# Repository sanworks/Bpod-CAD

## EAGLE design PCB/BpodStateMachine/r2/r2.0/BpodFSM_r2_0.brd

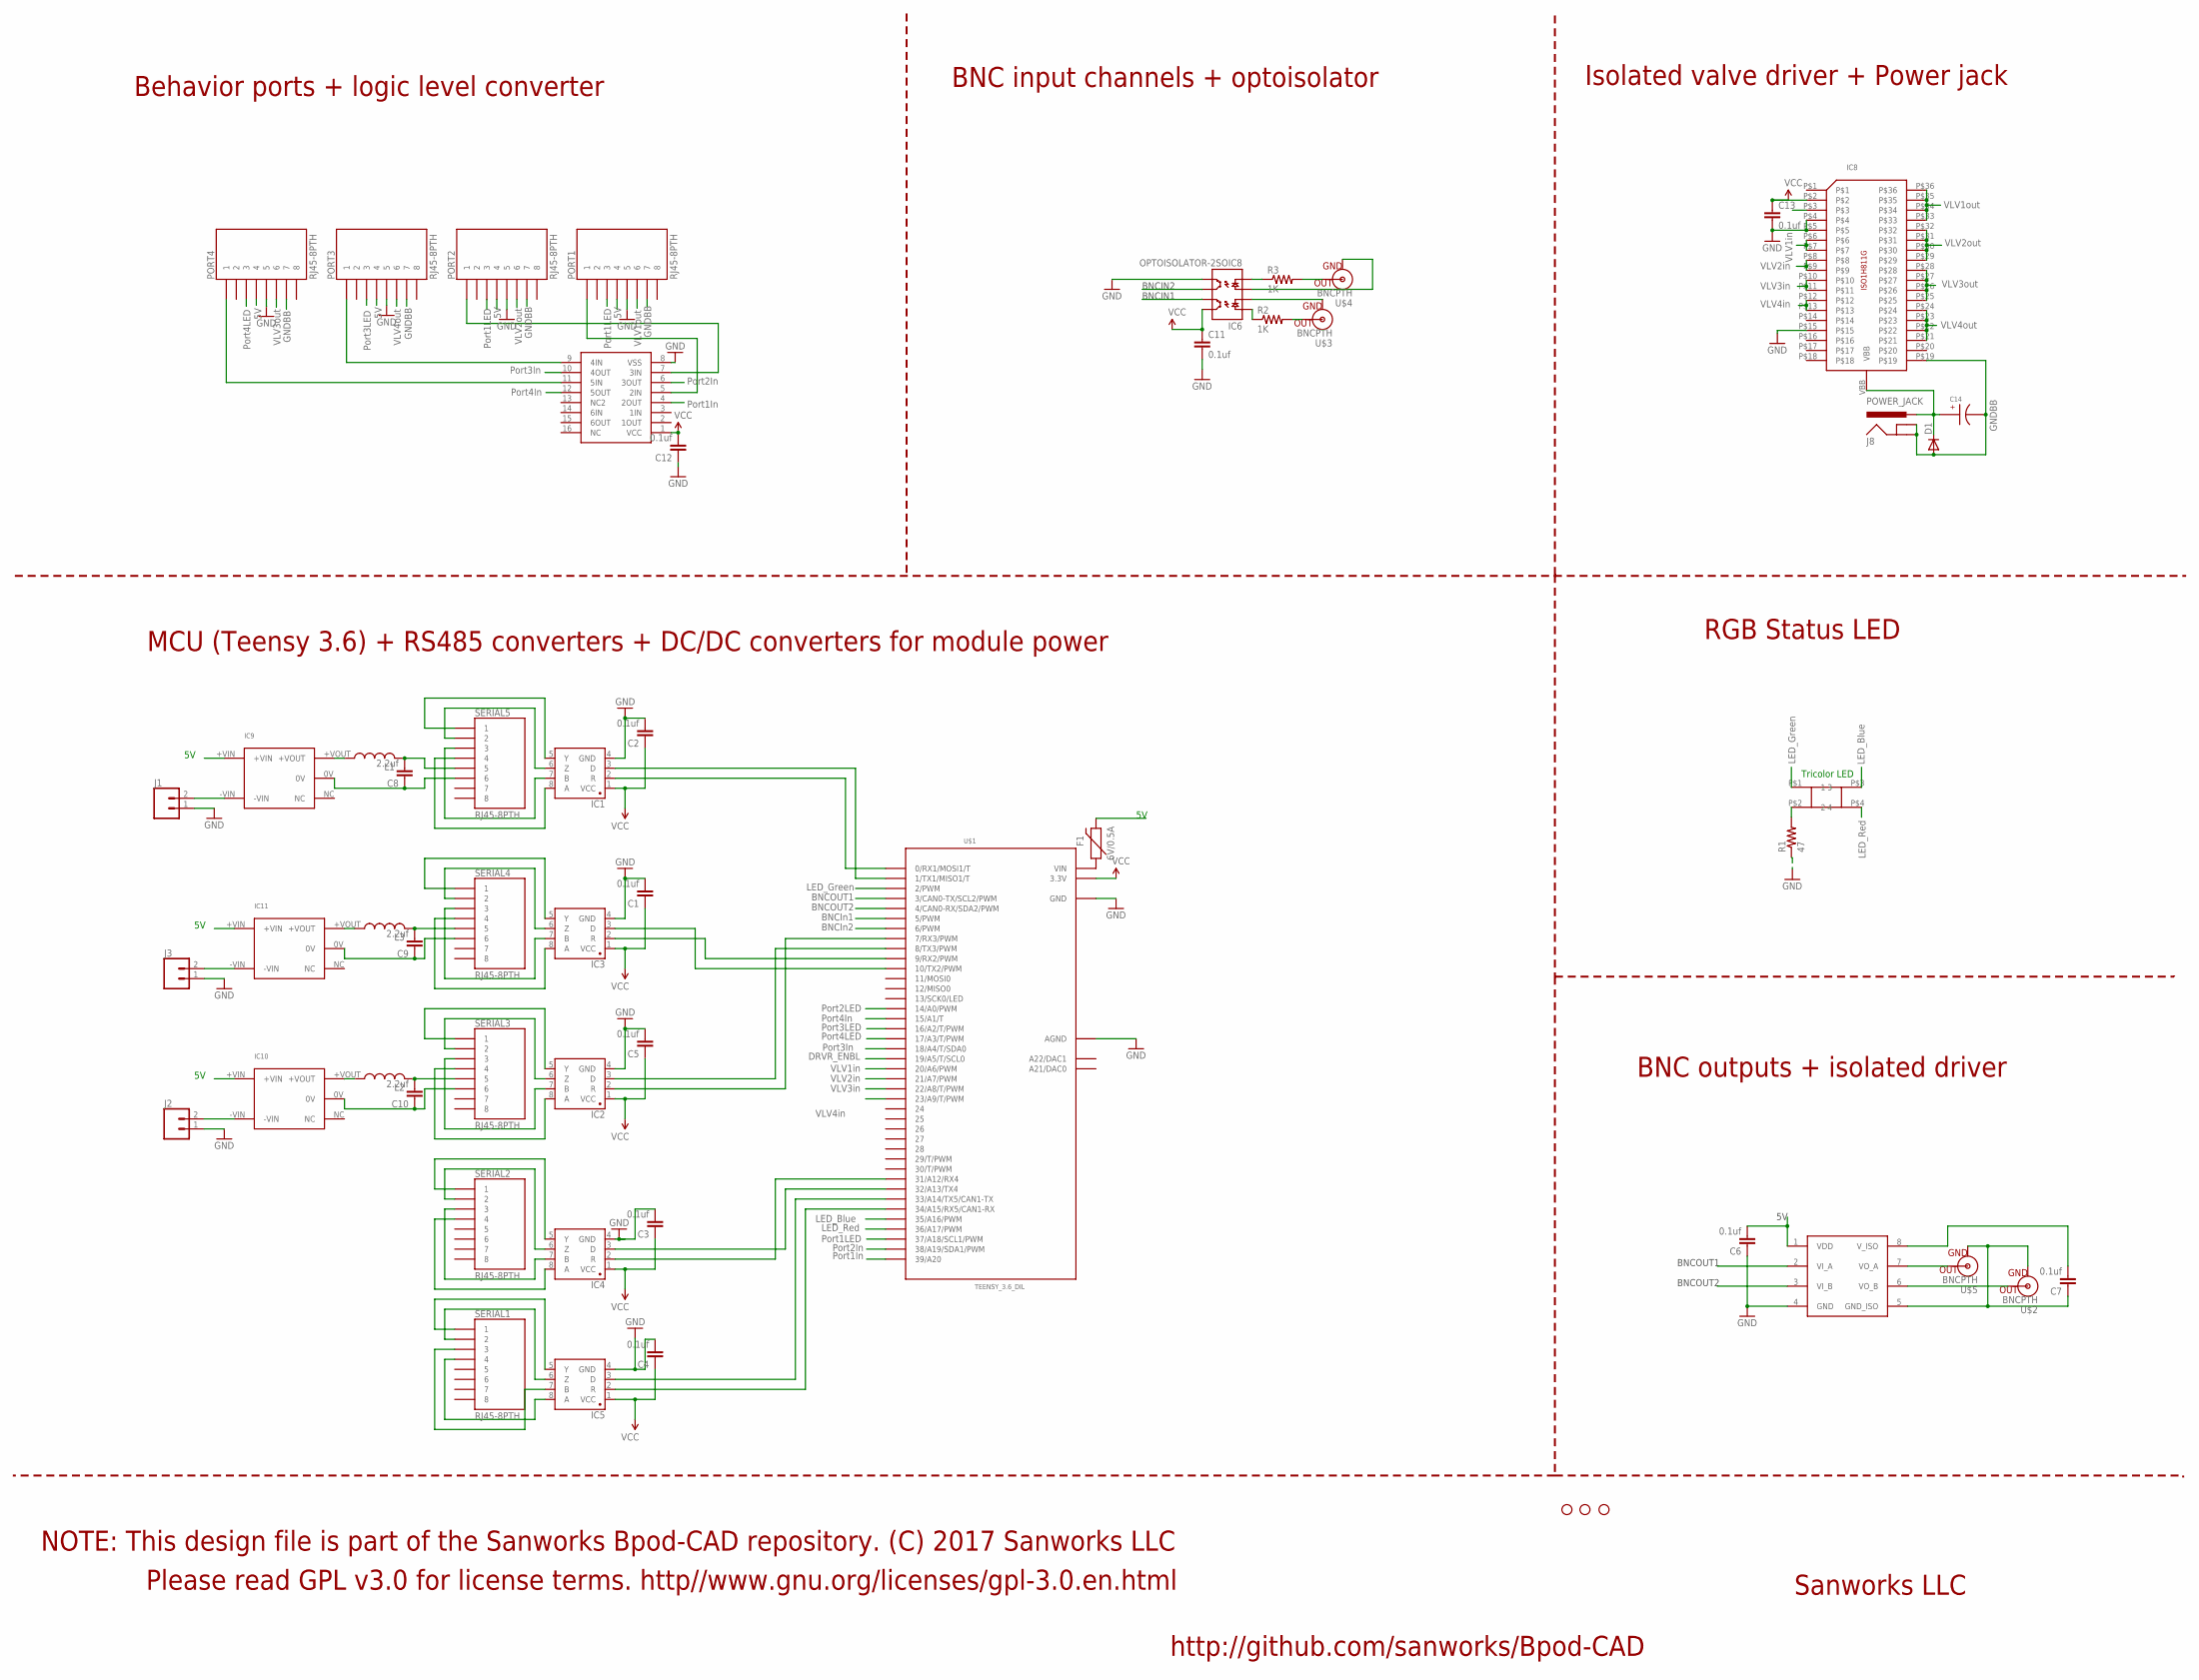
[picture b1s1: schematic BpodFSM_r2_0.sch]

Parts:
C1, C2, C3, C4, C5, C6, C7, C11, C12, C13: 0.1uf; 1206
C8, C9, C10: 2.2uf; 1206
C14: EEE-FK1H100UR
D1: DIODE-DO214AA; DO214AA
F1: 6V/0.5A; 1206
IC1, IC2, IC3, IC4, IC5: SN65HVD31DR; SO08
IC6: OPTOISOLATOR-2SOIC8; SO08-2
IC7: ADUM5240; SO08
IC8: ISO1H811G
IC9, IC10, IC11: MTU1D0505MC
IC12: CD4050; SO16
J1, J2, J3: CONN_02; 1X02
J8: POWER_JACK; POWER_JACK_PTH
JP3, JP4, JP5: STAND-OFF
L1, L2, L3: L-USL3225M; L3225M
PORT1, PORT2, PORT3, PORT4: RJ45-8PTH; RJ45-8
R1: 47; 1206
R2, R3: 1K; 1206
SERIAL1, SERIAL2, SERIAL3, SERIAL4, SERIAL5: RJ45-8PTH; RJ45-8
U$1: TEENSY_3.6_DIL
U$2, U$3, U$4, U$5: BNCPTH; BNC
U$8: SQUARE_TRICOLOR_LED

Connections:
5V: C6.2, F1.2, IC7.1 (VDD), IC9.+VIN, IC10.+VIN, IC11.+VIN, PORT1.4, PORT2.4, PORT3.4, PORT4.4
BNCIN1: IC6.7 (EM1), U$1.6 (6/PWM)
BNCIN2: IC6.6 (CL2), U$1.5 (5/PWM)
BNCOUT1: IC7.3 (VI_B), U$1.4 (4/CAN0-RX/SDA2/PWM)
BNCOUT2: IC7.2 (VI_A), U$1.3 (3/CAN0-TX/SCL2/PWM)
DRVR_ENBL: IC8.P$3, U$1.19/A5 (19/A5/T/SCL0)
GND: C1.2, C2.2, C3.2, C4.2, C5.2, C6.1, C11.2, C12.1, C13.2, IC1.4 (GND), IC2.4 (GND), IC3.4 (GND), IC4.4 (GND), IC5.4 (GND), IC6.5 (EM2), IC7.4 (GND), IC8.P$4, IC8.P$5, IC8.P$15, IC12.8 (VSS), J1.1, J2.1, J3.1, PORT1.5, PORT2.5, PORT3.5, PORT4.5, R1.1, U$1.AGND, U$1.GND, U$1.GND1 (GND)
GNDBB: C14.CATHODE, D1.A, IC8.P$19, J8.GND, J8.GNDBREAK, PORT1.7, PORT2.7, PORT3.7, PORT4.7
ISOGND: C7.1, IC7.5 (GND_ISO), U$2.GND, U$5.GND
LED_BLUE: U$1.35/A16 (35/A16/PWM), U$8.P$3 (3)
LED_GREEN: U$1.2 (2/PWM), U$8.P$1 (1)
LED_RED: U$1.36/A17 (36/A17/PWM), U$8.P$4 (4)
unnamed: IC3.8 (A), SERIAL4.4
unnamed: IC3.7 (B), SERIAL4.3
unnamed: IC3.6 (Z), SERIAL4.2
unnamed: IC3.5 (Y), SERIAL4.1
unnamed: IC3.2 (R), U$1.9 (9/RX2/PWM)
unnamed: IC3.3 (D), U$1.10 (10/TX2/PWM)
unnamed: IC1.8 (A), SERIAL5.4
unnamed: IC1.7 (B), SERIAL5.3
unnamed: IC1.6 (Z), SERIAL5.2
unnamed: IC1.5 (Y), SERIAL5.1
unnamed: IC1.2 (R), U$1.0 (0/RX1/MOSI1/T)
unnamed: IC1.3 (D), U$1.1 (1/TX1/MISO1/T)
unnamed: IC6.3 (A2), U$4.GND
unnamed: R3.2, U$4.S (OUT)
unnamed: R2.2, U$3.S (OUT)
unnamed: IC6.2 (C1), U$3.GND
unnamed: IC2.8 (A), SERIAL3.4
unnamed: IC2.7 (B), SERIAL3.3
unnamed: IC2.6 (Z), SERIAL3.2
unnamed: IC12.7 (3IN), PORT2.1
unnamed: IC2.5 (Y), SERIAL3.1
unnamed: IC2.2 (R), U$1.7 (7/RX3/PWM)
unnamed: C8.2, L1.2, SERIAL5.5
unnamed: IC12.9 (4IN), PORT3.1
unnamed: R1.2, U$8.P$2 (2)
unnamed: C8.1, IC9.0V, SERIAL5.6
unnamed: IC7.7 (VO_A), U$5.S (OUT)
unnamed: IC2.3 (D), U$1.8 (8/TX3/PWM)
unnamed: F1.1, U$1.VIN
unnamed: IC7.6 (VO_B), U$2.S (OUT)
unnamed: IC12.11 (5IN), PORT4.1
unnamed: IC5.8 (A), SERIAL1.4
unnamed: IC5.7 (B), SERIAL1.3
unnamed: IC5.6 (Z), SERIAL1.2
unnamed: IC5.5 (Y), SERIAL1.1
unnamed: IC4.8 (A), SERIAL2.4
unnamed: IC4.7 (B), SERIAL2.3
unnamed: IC4.6 (Z), SERIAL2.2
unnamed: IC9.+VOUT, L1.1
unnamed: IC4.5 (Y), SERIAL2.1
unnamed: IC9.-VIN, J1.2
unnamed: IC5.2 (R), U$1.34/A15 (34/A15/RX5/CAN1-RX)
unnamed: C10.1, IC10.0V, SERIAL3.6
unnamed: C10.2, L2.2, SERIAL3.5
unnamed: IC10.+VOUT, L2.1
unnamed: IC10.-VIN, J2.2
unnamed: C9.1, IC11.0V, SERIAL4.6
unnamed: IC5.3 (D), U$1.33/A14 (33/A14/TX5/CAN1-TX)
unnamed: C9.2, L3.2, SERIAL4.5
unnamed: IC11.+VOUT, L3.1
unnamed: IC11.-VIN, J3.2
unnamed: IC4.2 (R), U$1.31/A12 (31/A12/RX4)
unnamed: IC4.3 (D), U$1.32/A13 (32/A13/TX4)
unnamed: IC6.1 (A1), R2.1
unnamed: IC6.4 (C2), R3.1
unnamed: IC12.5 (2IN), PORT1.1
unnamed: C7.2, IC7.8 (V_ISO)
PORT1IN: IC12.4 (2OUT), U$1.39/A20
PORT1LED: PORT1.3, U$1.37/A18 (37/A18/SCL1/PWM)
PORT2IN: IC12.6 (3OUT), U$1.38/A19 (38/A19/SDA1/PWM)
PORT2LED: PORT2.3, U$1.14/A0 (14/A0/PWM)
PORT3IN: IC12.10 (4OUT), U$1.18/A4 (18/A4/T/SDA0)
PORT3LED: PORT3.3, U$1.16/A2 (16/A2/T/PWM)
PORT4IN: IC12.12 (5OUT), U$1.15/A1 (15/A1/T)
PORT4LED: PORT4.3, U$1.17/A3 (17/A3/T/PWM)
VBB: C14.ANODE, D1.C, IC8.VBB, J8.PWR
VCC: C1.1, C2.1, C3.1, C4.1, C5.1, C11.1, C12.2, C13.1, IC1.1 (VCC), IC2.1 (VCC), IC3.1 (VCC), IC4.1 (VCC), IC5.1 (VCC), IC6.8 (CL1), IC8.P$2, IC12.1 (VCC), U$1.3.3V, U$1.3.3V3 (3.3V)
VLV1IN: IC8.P$6, IC8.P$7, U$1.23/A9 (23/A9/T/PWM)
VLV1OUT: IC8.P$33, IC8.P$34, IC8.P$35, IC8.P$36, PORT1.6
VLV2IN: IC8.P$8, IC8.P$9, U$1.22/A8 (22/A8/T/PWM)
VLV2OUT: IC8.P$29, IC8.P$30, IC8.P$31, IC8.P$32, PORT2.6
VLV3IN: IC8.P$12, IC8.P$13, U$1.20/A6 (20/A6/PWM)
VLV3OUT: IC8.P$21, IC8.P$22, IC8.P$23, IC8.P$24, PORT3.6
VLV4IN: IC8.P$10, IC8.P$11, U$1.21/A7 (21/A7/PWM)
VLV4OUT: IC8.P$25, IC8.P$26, IC8.P$27, IC8.P$28, PORT4.6

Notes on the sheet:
Tricolor LED
LED_Blue
LED_Red
LED_Green
BNCIN1
BNCIN2
BNCIn1
BNCIn2
BNCOUT2
BNCOUT1
Port1In
Port2In
Port3In
Port4In
Port1LED
Port2LED
Port3LED
Port4LED
DRVR_ENBL
VLV2in
VLV3in
VLV4in
VLV1in
GNDBB
VLV1out
VLV2out
VLV3out
VLV4out
Sanworks LLC
http://github.com/sanworks/Bpod-CAD
Please read GPL v3.0 for license terms. http//www.gnu.org/licenses/gpl-3.0.en.html
NOTE: This design file is part of the Sanworks Bpod-CAD repository. (C) 2017 Sanworks LLC
Behavior ports + logic level converter
BNC input channels + optoisolator
Isolated valve driver + Power jack
RGB Status LED
BNC outputs + isolated driver
MCU (Teensy 3.6) + RS485 converters + DC/DC converters for module power

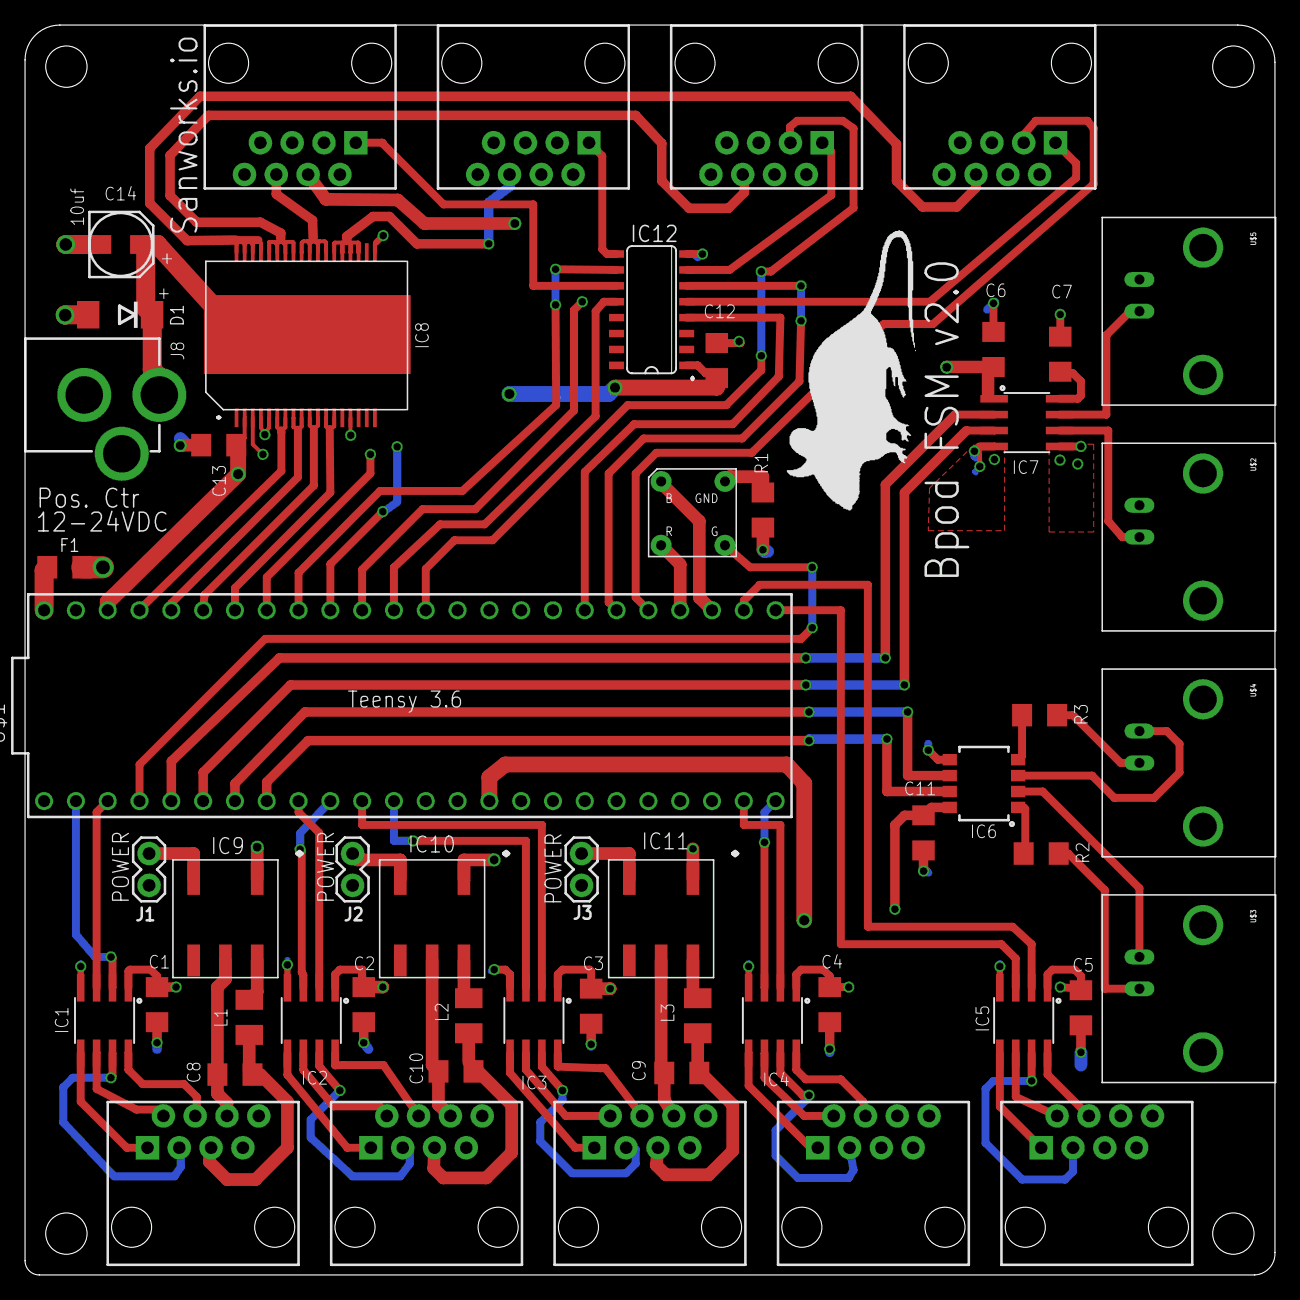
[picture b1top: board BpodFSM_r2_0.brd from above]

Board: 4 copper layers, 99.8 x 99.8 mm, 58 parts (0 on the bottom side), 87 nets.

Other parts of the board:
JP1: STAND-OFF
U$9: MOUSELOGO

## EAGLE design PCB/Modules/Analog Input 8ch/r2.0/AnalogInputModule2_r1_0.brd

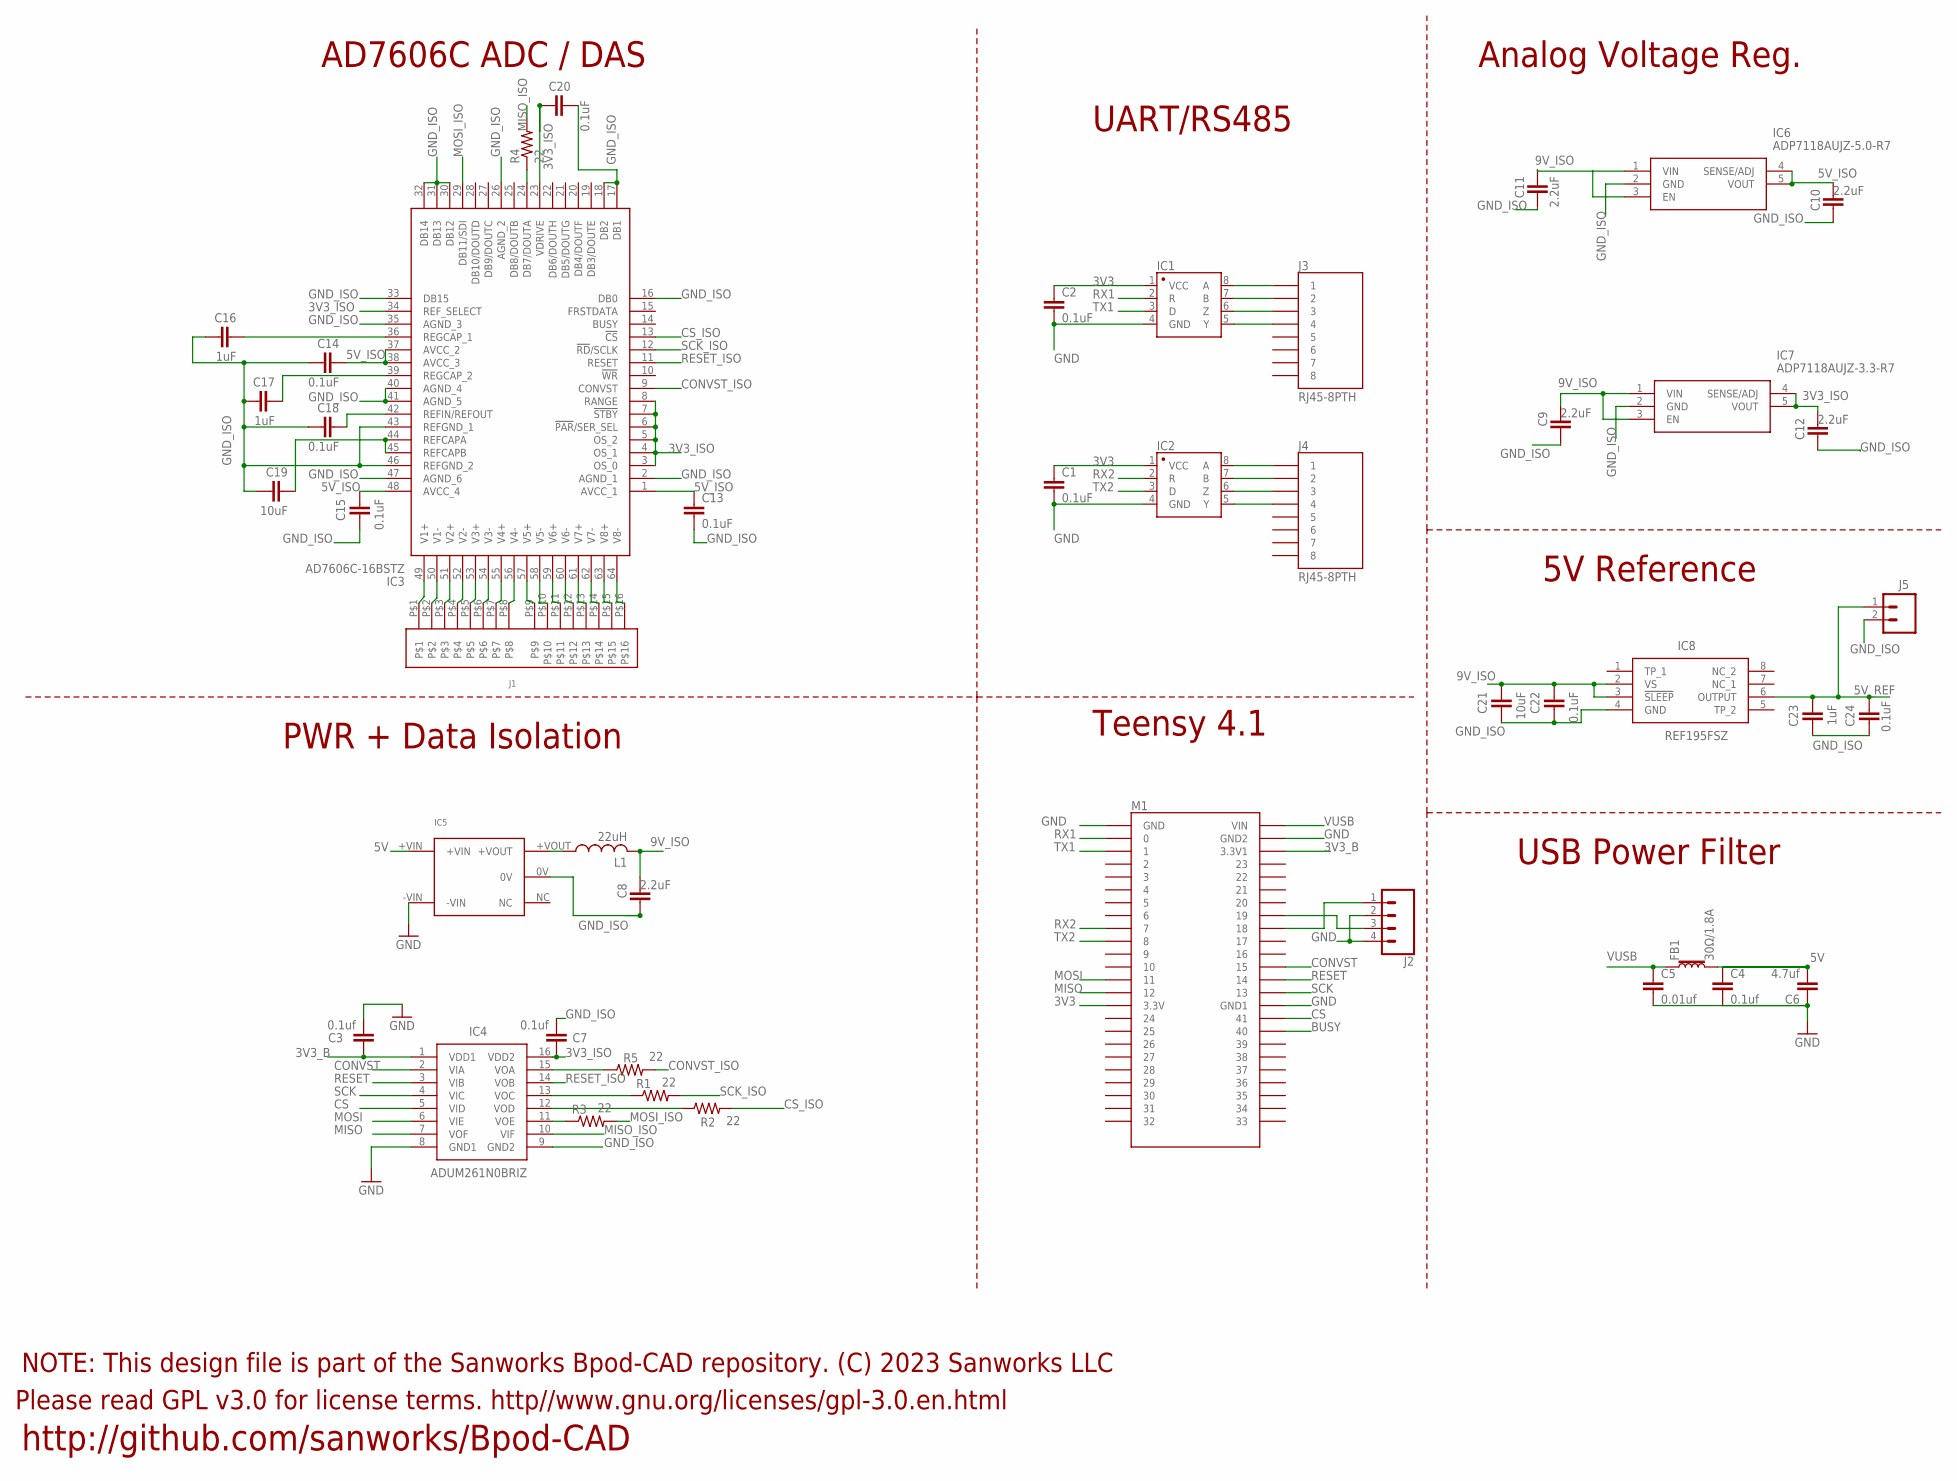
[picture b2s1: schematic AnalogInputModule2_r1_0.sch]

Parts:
C1, C2, C13, C14, C15, C18, C20, C22, C24: 0.1uF; 0805
C3, C4, C7: 0.1uf; 0805
C5: 0.01uf; 0805
C6: 4.7uf; 1206@2
C8, C9, C10, C11, C12: 2.2uF; 0805
C16, C17, C23: 1uF; 0805
C19, C21: 10uF; 0805
FB1: 30Ω/1.8A; 0603
IC1, IC2: SN65HVD31DR; SO08
IC3: AD7606C-16BSTZ; QFP50P1200X1200X160-64N
IC4: ADUM261N0BRIZ; SOIC127P1030X264-16N
IC5: 5V; MTU1D0505MC
IC6: ADP7118AUJZ-5.0-R7; SOT95P280X100-5N
IC7: ADP7118AUJZ-3.3-R7; SOT95P280X100-5N
IC8: REF195FSZ; SOIC127P600X175-8N
J1: 16POS_MOLEX_SOCKET
J2: CONN_04SCREW_LOCK; SCREWTERMINAL-3.5MM-4_LOCK
J3, J4: RJ45-8PTH; RJ45-8
J5: CONN_023.5MM_LOCK; SCREWTERMINAL-3.5MM-2_LOCK
L1: 22uH; L3225M
M1: TEENSY4.1_SIDESONLY
R1, R2, R3, R4, R5: 22; R0805

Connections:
3V3: C1.1, C2.1, IC1.1 (VCC), IC2.1 (VCC), M1.3V3 (3.3V)
3V3_B: C3.1, IC4.1 (VDD1), M1.3V3_LO (3.3V1)
3V3_ISO: C7.1, C12.2, C20.1, IC3.3 (OS_0), IC3.4 (OS_1), IC3.5 (OS_2), IC3.6 (!PAR!/SER_SEL), IC3.7 (!STBY), IC3.8 (RANGE), IC3.23 (VDRIVE), IC3.34 (REF_SELECT), IC4.16 (VDD2), IC7.4 (SENSE/ADJ), IC7.5 (VOUT)
5V: C4.1, C6.2, FB1.2, IC5.+VIN
5V_ISO: C10.2, C13.1, C14.2, C15.2, IC3.1 (AVCC_1), IC3.37 (AVCC_2), IC3.38 (AVCC_3), IC3.48 (AVCC_4), IC6.4 (SENSE/ADJ), IC6.5 (VOUT)
5V_REF: C23.2, C24.2, IC8.6 (OUTPUT), J5.1
9V_ISO: C8.2, C9.2, C11.2, C21.2, C22.2, IC6.1 (VIN), IC6.3 (EN), IC7.1 (VIN), IC7.3 (EN), IC8.2 (VS), IC8.3 (!SLEEP), L1.2
BUSY: M1.40
CONVST: IC4.2 (VIA), M1.15/A1 (15)
CONVST_ISO: IC3.9 (CONVST), R5.2
CS: IC4.5 (VID), M1.41
CS_ISO: IC3.13 (!CS), R2.2
GND: C1.2, C2.2, C3.2, C4.2, C5.2, C6.1, IC1.4 (GND), IC2.4 (GND), IC4.8 (GND1), IC5.-VIN, J2.2, J2.4, M1.AGND (GND), M1.GND (GND1), M1.GND1 (GND2)
GND_ISO: C7.2, C8.1, C9.1, C10.1, C11.1, C12.1, C13.2, C14.1, C15.1, C16.1, C17.1, C18.1, C19.1, C20.2, C21.1, C22.1, C23.1, C24.1, IC3.2 (AGND_1), IC3.16 (DB0), IC3.17 (DB1), IC3.18 (DB2), IC3.26 (AGND_2), IC3.30 (DB12), IC3.31 (DB13), IC3.32 (DB14), IC3.33 (DB15), IC3.35 (AGND_3), IC3.40 (AGND_4), IC3.41 (AGND_5), IC3.43 (REFGND_1), IC3.46 (REFGND_2), IC3.47 (AGND_6), IC4.9 (GND2), IC5.0V, IC6.2 (GND), IC7.2 (GND), IC8.4 (GND), J5.2
MISO: IC4.7 (VOF), M1.12/MISO (12)
MISO_ISO: IC4.10 (VIF), R4.2
MOSI: IC4.6 (VIE), M1.11/MOSI (11)
MOSI_ISO: IC3.29 (DB11/SDI), R3.2
unnamed: IC1.6 (Z), J3.3
unnamed: IC1.8 (A), J3.1
unnamed: IC1.5 (Y), J3.4
unnamed: IC1.7 (B), J3.2
unnamed: IC2.6 (Z), J4.3
unnamed: IC2.5 (Y), J4.4
unnamed: IC2.8 (A), J4.1
unnamed: IC2.7 (B), J4.2
unnamed: IC3.64 (V8-), J1.P$16
unnamed: IC3.63 (V8+), J1.P$15
unnamed: IC3.62 (V7-), J1.P$14
unnamed: IC3.61 (V7+), J1.P$13
unnamed: IC3.60 (V6-), J1.P$12
unnamed: IC3.59 (V6+), J1.P$11
unnamed: IC3.58 (V5-), J1.P$10
unnamed: IC3.57 (V5+), J1.P$9
unnamed: IC3.56 (V4-), J1.P$8
unnamed: IC3.55 (V4+), J1.P$7
unnamed: IC3.54 (V3-), J1.P$6
unnamed: IC3.53 (V3+), J1.P$5
unnamed: IC3.52 (V2-), J1.P$4
unnamed: IC3.51 (V2+), J1.P$3
unnamed: IC3.50 (V1-), J1.P$2
unnamed: IC3.49 (V1+), J1.P$1
unnamed: IC4.13 (VOC), R1.1
unnamed: IC4.12 (VOD), R2.1
unnamed: IC4.11 (VOE), R3.1
unnamed: IC3.24 (DB7/DOUTA), R4.1
unnamed: IC4.15 (VOA), R5.1
unnamed: C16.2, IC3.36 (REGCAP_1)
unnamed: C17.2, IC3.39 (REGCAP_2)
unnamed: C18.2, IC3.42 (REFIN/REFOUT)
unnamed: C19.2, IC3.44 (REFCAPA), IC3.45 (REFCAPB)
unnamed: J2.1, M1.18/A4/SDA (18)
unnamed: IC5.+VOUT, L1.1
unnamed: J2.3, M1.19/A5/SCL (19)
RESET: IC4.3 (VIB), M1.14/A0 (14)
RESET_ISO: IC3.11 (RESET), IC4.14 (VOB)
RX1: IC1.2 (R), M1.0/RX (0)
RX2: IC2.2 (R), M1.7
SCK: IC4.4 (VIC), M1.13/SCK (13)
SCK_ISO: IC3.12 (!RD!/SCLK), R1.2
TX1: IC1.3 (D), M1.1/TX (1)
TX2: IC2.3 (D), M1.8
VUSB: C5.1, FB1.1, M1.VIN

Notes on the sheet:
Teensy 4.1
UART/RS485
USB Power Filter
AD7606C ADC / DAS
PWR + Data Isolation
Analog Voltage Reg.
5V Reference
Please read GPL v3.0 for license terms. http//www.gnu.org/licenses/gpl-3.0.en.html
NOTE: This design file is part of the Sanworks Bpod-CAD repository. (C) 2023 Sanworks LLC
http://github.com/sanworks/Bpod-CAD

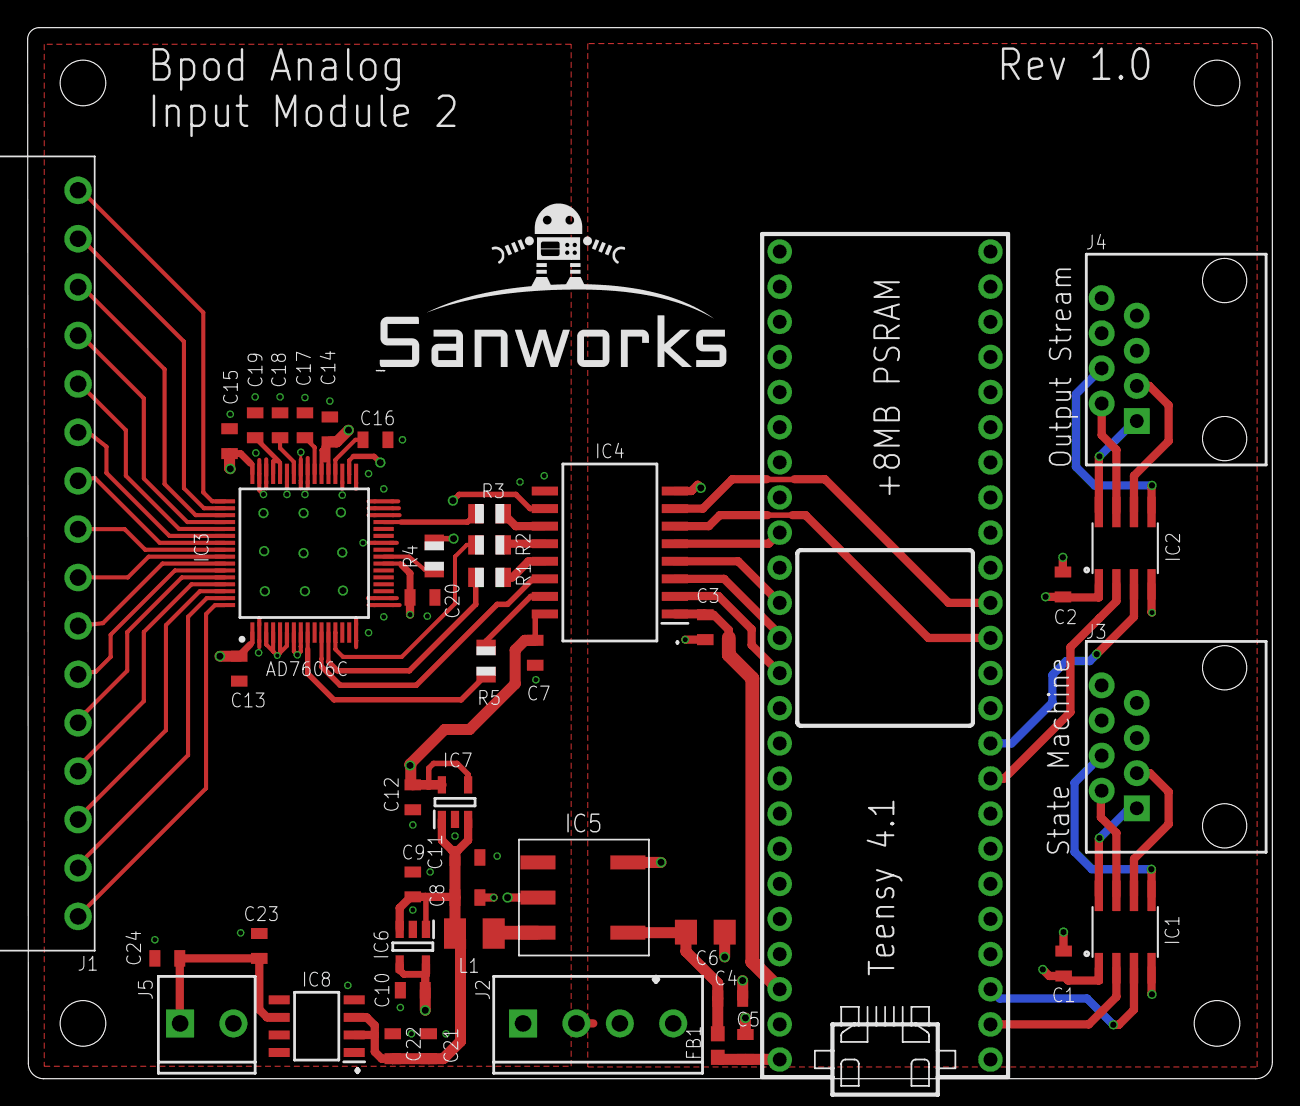
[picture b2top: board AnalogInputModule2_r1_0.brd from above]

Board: 4 copper layers, 90.0 x 76.0 mm, 50 parts (0 on the bottom side), 62 nets.

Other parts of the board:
U$1: SANWORKS_LOGO
U$5, U$6, U$7, U$8: STAND-OFF

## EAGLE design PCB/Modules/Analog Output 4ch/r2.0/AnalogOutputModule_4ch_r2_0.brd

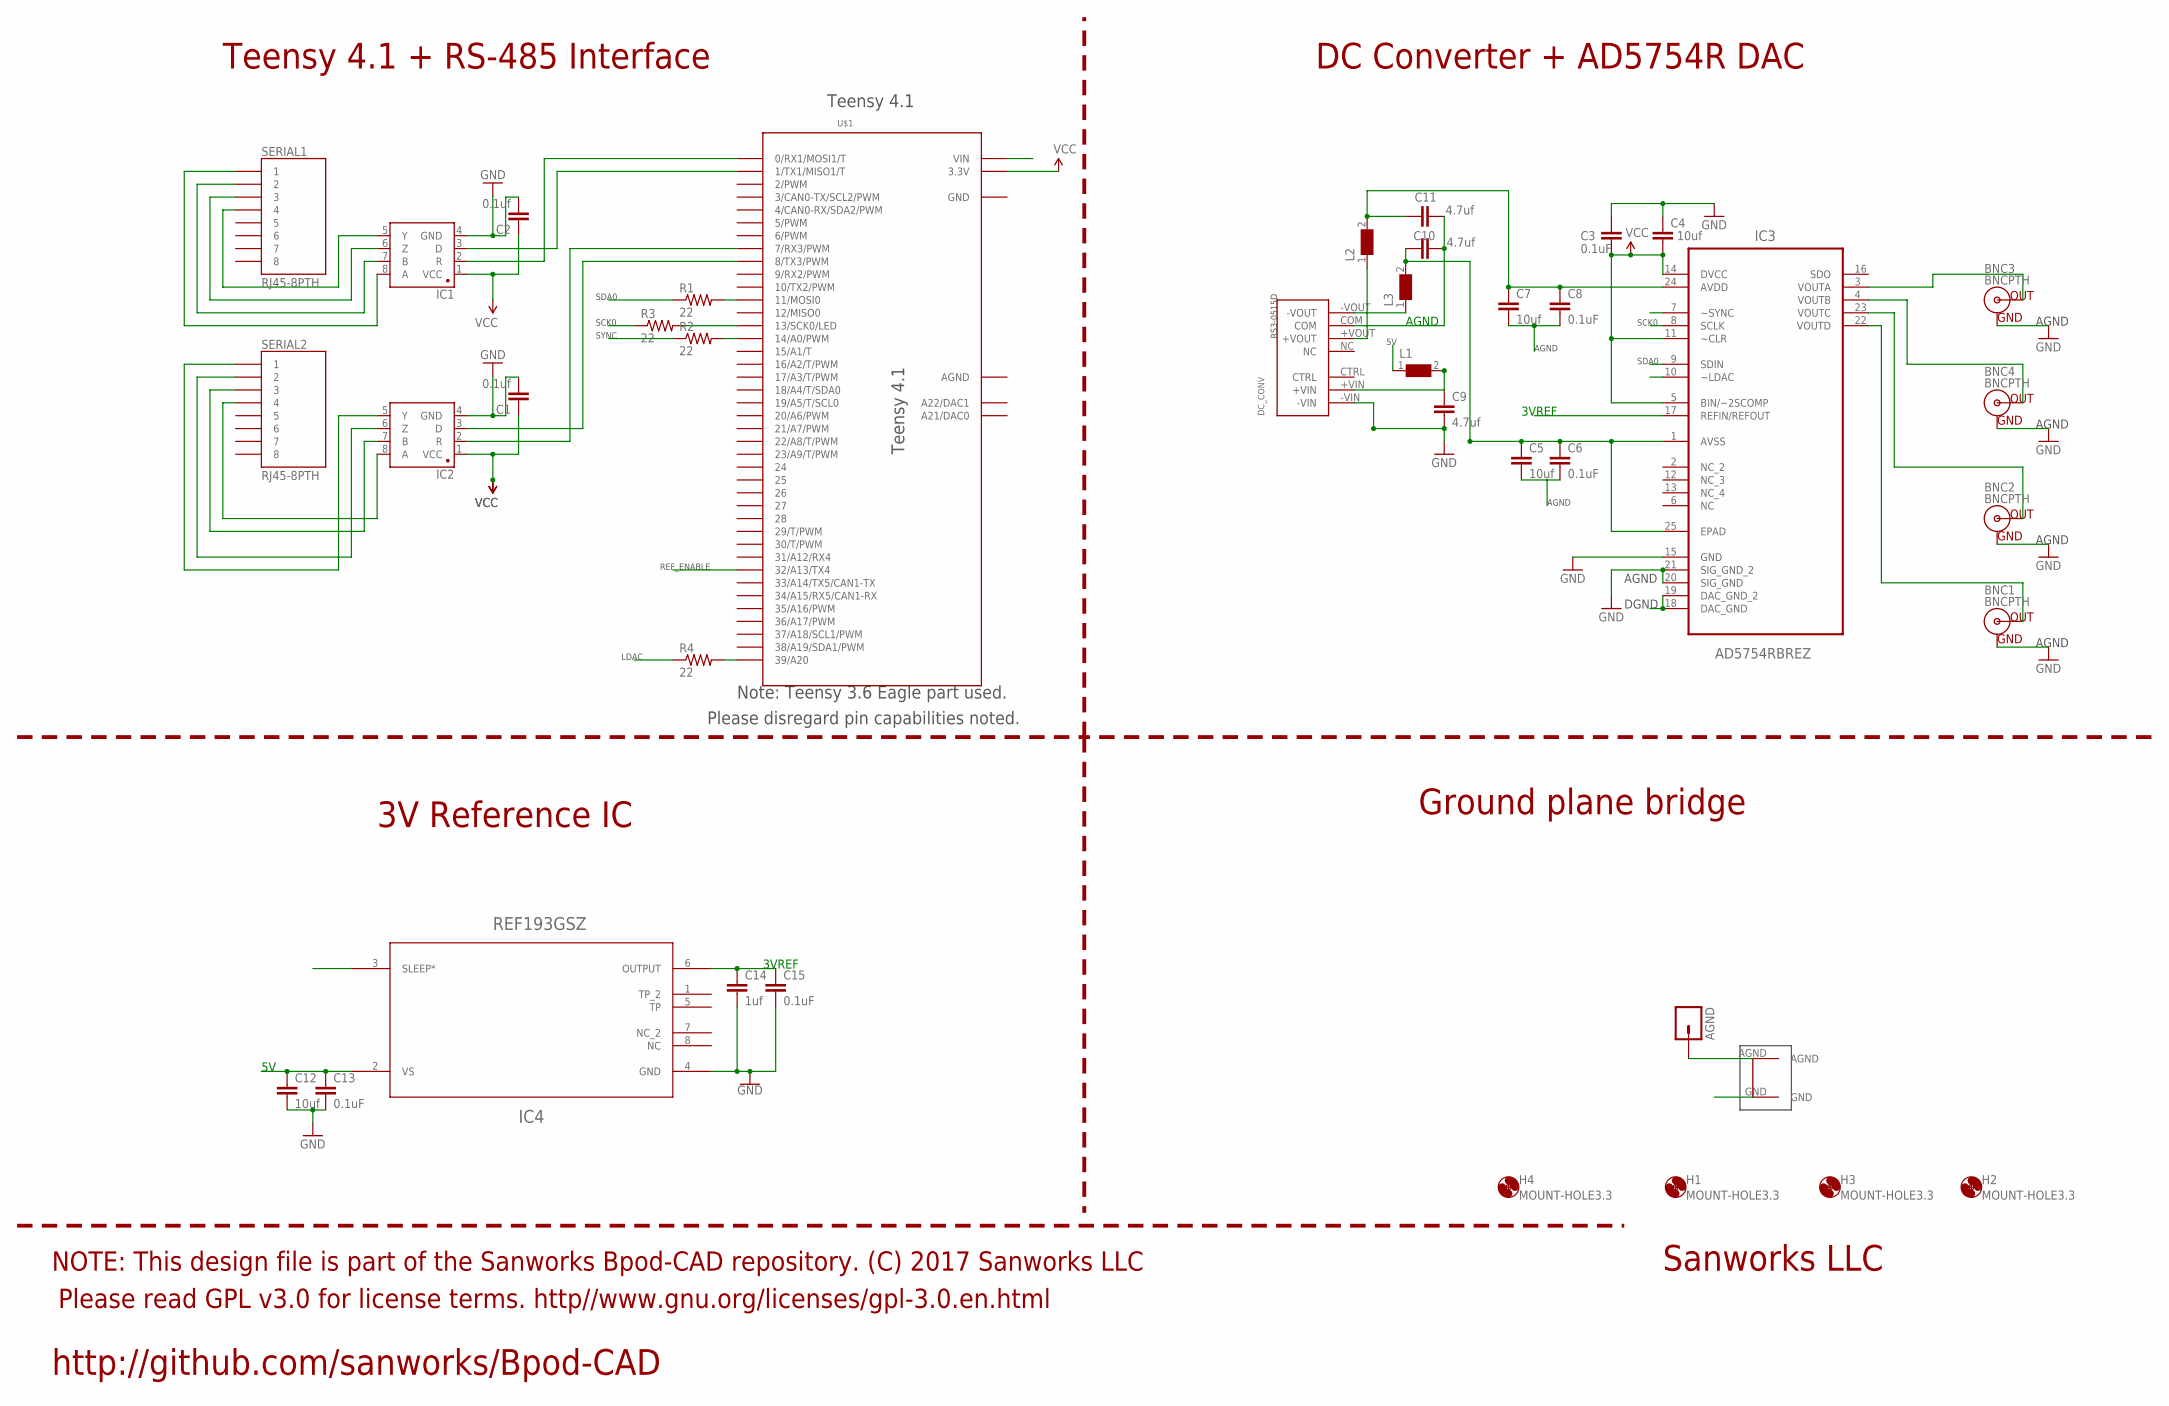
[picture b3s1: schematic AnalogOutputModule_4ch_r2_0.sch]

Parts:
AGND: M01PTH; 1X01
BNC1, BNC2, BNC3, BNC4: BNCPTH; BNC
C1, C2: 0.1uf; 1206@1
C3, C6, C8, C13, C15: 0.1uF; 0805
C4, C5, C7, C12: 10uf; 1206@1
C9, C10, C11: 4.7uf; 1206@1
C14: 1uf; 1206@1
DC_CONV: RS3-0515D
H1, H2, H3, H4: MOUNT-HOLE3.3; 3,3
IC1, IC2: SN65HVD31DR; SO08
IC3: AD5754RBREZ; SOP65P640X120-25N
IC4: REF193GSZ; R_8
L1, L2, L3: WE-CBF-742792118_1206; 1206
R1, R2, R3, R4: 22; 1206
SERIAL1, SERIAL2: RJ45-8PTH; RJ45-8
U$1: TEENSY_3.6_DIL
U$6: GNDPLANESHRT

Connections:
3VREF: C14.1, C15.1, IC3.17 (REFIN/REFOUT), IC4.6 (OUTPUT)
5V: C3.2, C4.2, C12.1, C13.1, IC3.5 (BIN/~2SCOMP), IC3.11 (~CLR), IC3.14 (DVCC), IC4.2 (VS), L1.1, U$1.VIN
AGND: AGND.1, BNC1.GND, BNC2.GND, BNC3.GND, BNC4.GND, C5.2, C6.2, C7.2, C8.2, C10.1, C11.2, DC_CONV.COM, IC3.18 (DAC_GND), IC3.19 (DAC_GND_2), IC3.20 (SIG_GND), IC3.21 (SIG_GND_2), U$1.AGND, U$6.AGND
GND: C1.2, C2.2, C3.1, C4.1, C9.2, C12.2, C13.2, C14.2, C15.2, DC_CONV.-VIN, IC1.4 (GND), IC2.4 (GND), IC3.15 (GND), IC4.4 (GND), U$1.GND, U$1.GND1 (GND), U$6.GND
LDAC: IC3.10 (~LDAC), R4.1
unnamed: IC1.3 (D), U$1.1 (1/TX1/MISO1/T)
unnamed: IC1.2 (R), U$1.0 (0/RX1/MOSI1/T)
unnamed: IC2.8 (A), SERIAL2.4
unnamed: IC2.7 (B), SERIAL2.3
unnamed: IC2.6 (Z), SERIAL2.2
unnamed: IC2.5 (Y), SERIAL2.1
unnamed: IC2.3 (D), U$1.8 (8/TX3/PWM)
unnamed: IC2.2 (R), U$1.7 (7/RX3/PWM)
unnamed: BNC3.S (OUT), IC3.3 (VOUTA)
unnamed: BNC4.S (OUT), IC3.4 (VOUTB)
unnamed: BNC2.S (OUT), IC3.23 (VOUTC)
unnamed: BNC1.S (OUT), IC3.22 (VOUTD)
unnamed: R1.2, U$1.11 (11/MOSI0)
unnamed: R3.2, U$1.13 (13/SCK0/LED)
unnamed: DC_CONV.-VOUT, L3.1
unnamed: DC_CONV.+VOUT, L2.1
unnamed: R2.2, U$1.14/A0 (14/A0/PWM)
unnamed: R4.2, U$1.39/A20
unnamed: IC1.8 (A), SERIAL1.1
unnamed: IC1.7 (B), SERIAL1.2
unnamed: IC1.6 (Z), SERIAL1.3
unnamed: IC1.5 (Y), SERIAL1.4
unnamed: C7.1, C8.1, C10.2, IC3.24 (AVDD), L2.2
unnamed: C9.1, DC_CONV.+VIN, L1.2
REF_ENABLE: IC4.3 (SLEEP*), U$1.32/A13 (32/A13/TX4)
SCK0: IC3.8 (SCLK), R3.1
SDA0: IC3.9 (SDIN), R1.1
SYNC: IC3.7 (~SYNC), R2.1
VCC: C1.1, C2.1, IC1.1 (VCC), IC2.1 (VCC), U$1.3.3V, U$1.3.3V3 (3.3V)
VSS: C5.1, C6.1, C11.1, IC3.1 (AVSS), IC3.25 (EPAD), L3.2

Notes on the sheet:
AGND
SCK0
SDA0
DGND
SYNC
LDAC
3VREF
REF_ENABLE
Teensy 4.1 + RS-485 Interface
DC Converter + AD5754R DAC
3V Reference IC
Ground plane bridge
Please read GPL v3.0 for license terms. http//www.gnu.org/licenses/gpl-3.0.en.html
NOTE: This design file is part of the Sanworks Bpod-CAD repository. (C) 2017 Sanworks LLC
Sanworks LLC
http://github.com/sanworks/Bpod-CAD
Teensy 4.1
Note: Teensy 3.6 Eagle part used.
Please disregard pin capabilities noted.

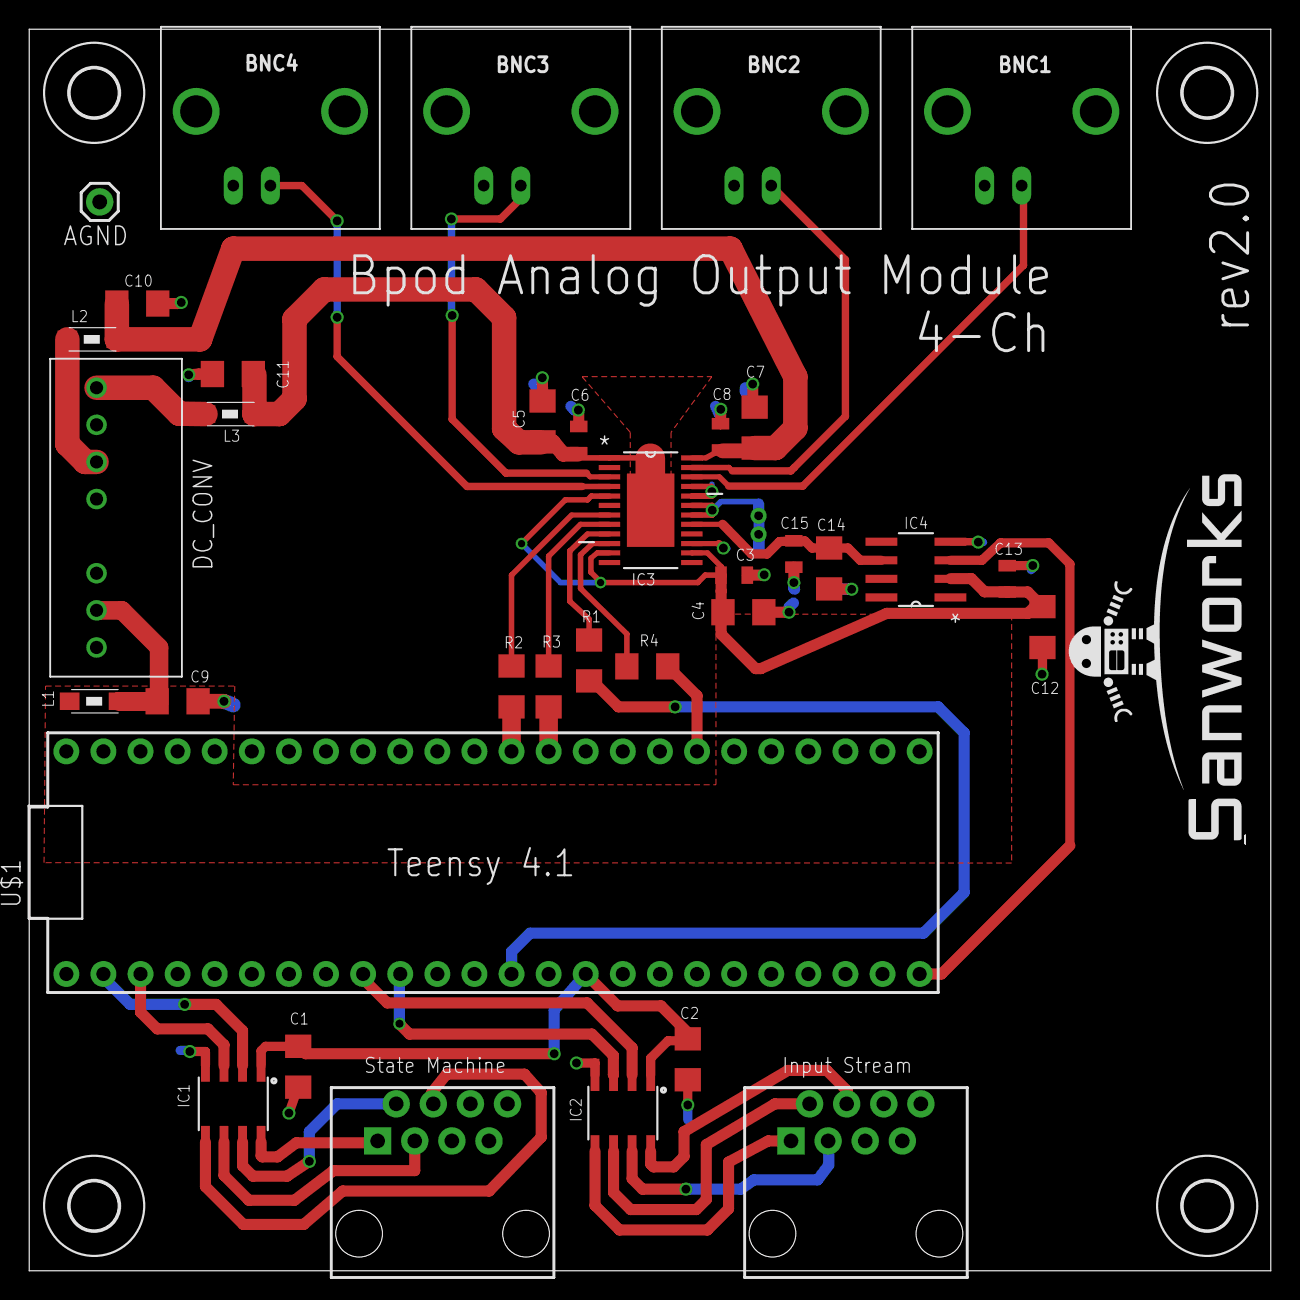
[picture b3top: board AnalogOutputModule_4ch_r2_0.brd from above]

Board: 2 copper layers, 85.0 x 85.0 mm, 41 parts (0 on the bottom side), 35 nets.

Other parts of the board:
U$2: SANWORKS_LOGO

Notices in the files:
parts and their libraries:
SparkFun-Capacitors: Licensing: Creative Commons ShareAlike 4.0 International - https://creativecommons.org/licenses/by-sa/4.0
SparkFun-Passives: Licensing: CC v3.0 Share-Alike You are welcome to use this library for commercial purposes.
